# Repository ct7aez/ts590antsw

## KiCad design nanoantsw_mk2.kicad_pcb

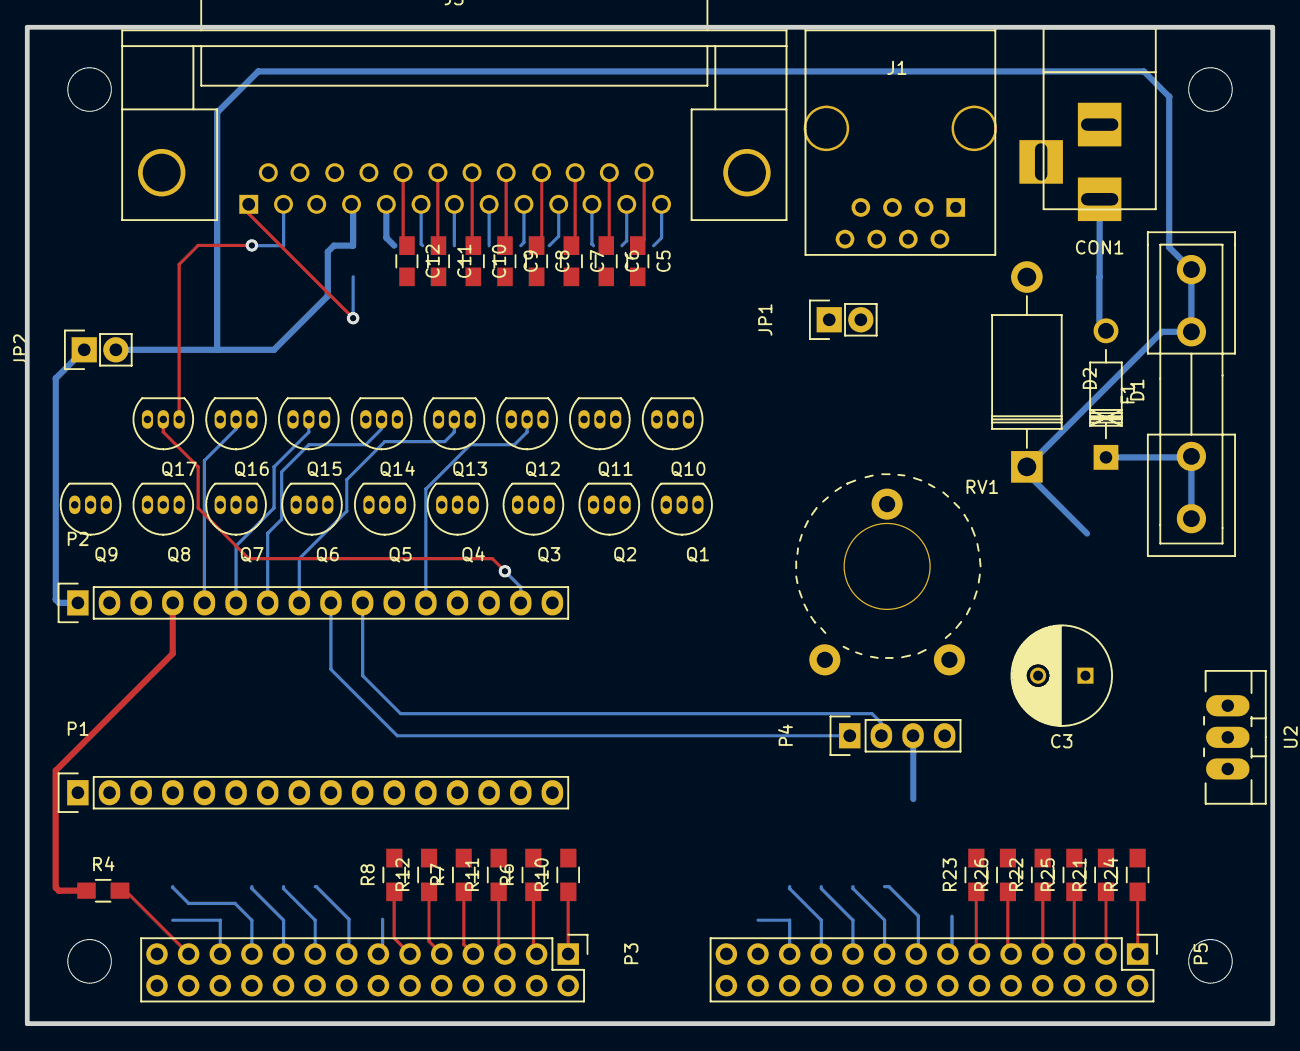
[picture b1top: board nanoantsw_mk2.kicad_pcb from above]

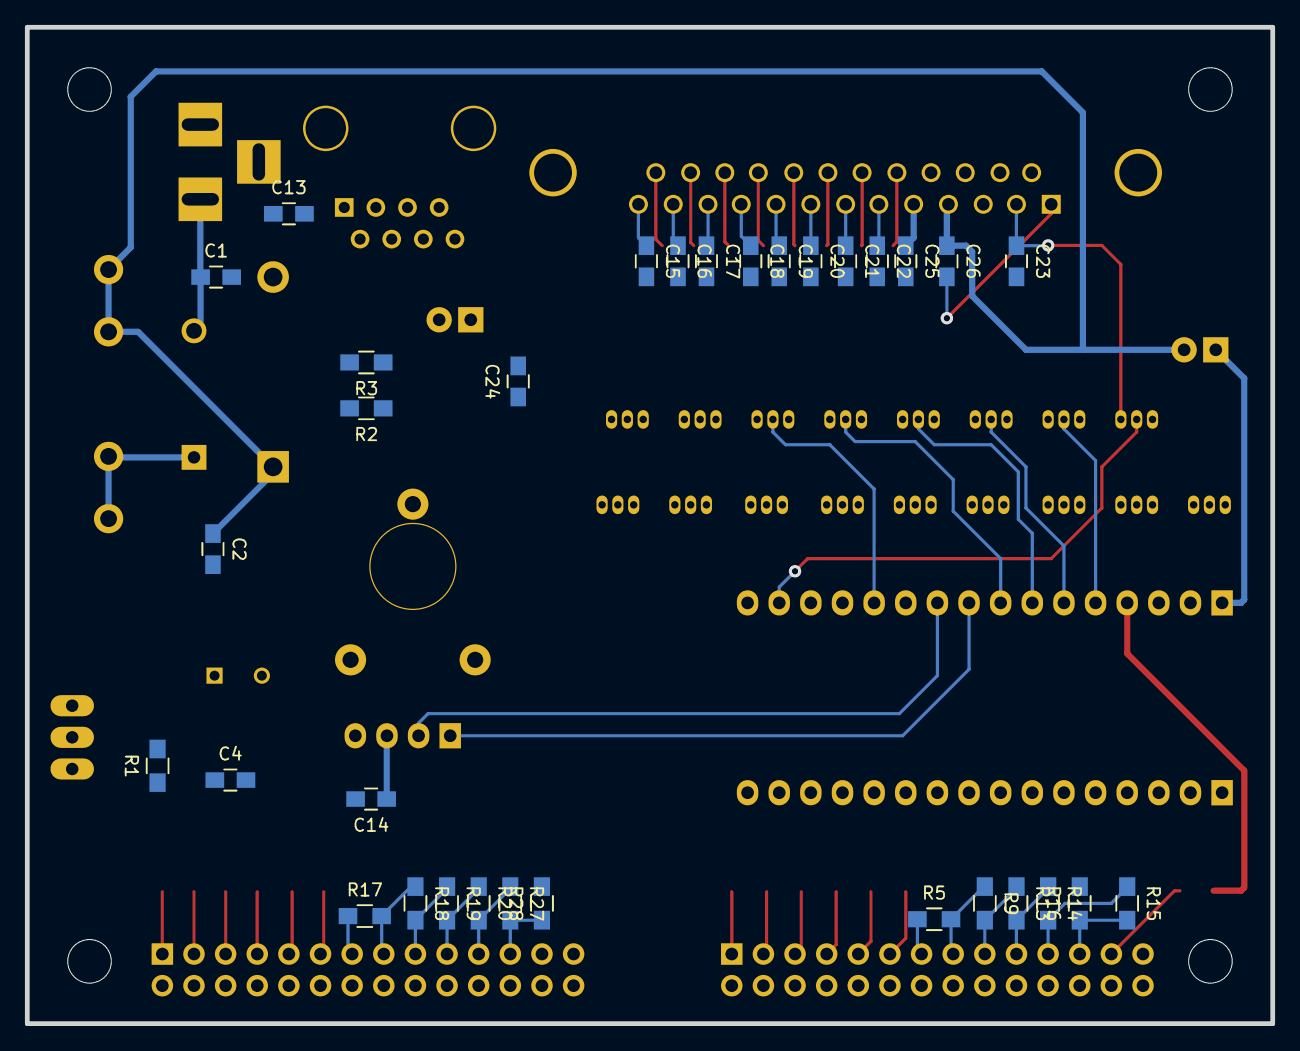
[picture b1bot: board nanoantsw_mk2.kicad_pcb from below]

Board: 2 copper layers, 100.0 x 80.0 mm, 86 parts (32 on the bottom side), 71 nets.

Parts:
C1: 4n7; C_0805_HandSoldering
C2: 330n; C_0805_HandSoldering
C3: 220u; C_Radial_D8_L21_P3.8
C4, C25, C26: 100n; C_0805_HandSoldering
C5, C6, C7, C8, C9, C10, C11, C12, C13, C14, C15, C16, C17, C18, C19, C20, C21, C22, C23, C24: 10n; C_0805_HandSoldering
CON1: 5,5/2,1mm; BARREL_JACK
D1: 1N5817; Diode_DO-41_SOD81_Horizontal_RM10
D2: 1.5KE20A; Diode_DO-201AD_Horizontal_RM15
F1: 500mAT; Fuseholder5x20_horiz_open_inline_Type-I
J1: RJ45; RJ45_8
J3: DB25; DB25FC
JP1, JP2: Jumper_NO_Small; Pin_Header_Straight_1x02
P1, P2: CONN_01X16; Socket_Strip_Straight_1x16
P3, P5: CONN_02X14; Pin_Header_Straight_2x14
P4: CONN_01X04; Pin_Header_Straight_1x04
Q1, Q2, Q3, Q4, Q5, Q6, Q7, Q8, Q9, Q10, Q11, Q12, Q13, Q14, Q15, Q16, Q17: BS170; TO-92_Inline_Narrow_Oval
R1: 240R; R_0805_HandSoldering
R2, R3: 2K; R_0805_HandSoldering
R4, R16: 3K3; R_0805_HandSoldering
R5: 100R; R_0805_HandSoldering
R6, R7, R8, R10, R11, R12, R21, R22, R23, R24, R25, R26: 330R; R_0805_HandSoldering
R9: 200R; R_0805_HandSoldering
R13: 390R; R_0805_HandSoldering
R14: 820R; R_0805_HandSoldering
R15: 1K6; R_0805_HandSoldering
R17: 6K8; R_0805_HandSoldering
R18: 13K; R_0805_HandSoldering
R19: 27K; R_0805_HandSoldering
R20: 62K; R_0805_HandSoldering
R27: 120K; R_0805_HandSoldering
R28: 240K; R_0805_HandSoldering
RV1: 5K; Potentiometer_Trimmer-Piher_PT15-V12-5_horizontal_revers
U2: LM317AT; TO-220_Neutral123_Vertical_LargePads

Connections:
+5V: C14.1, J1.2, JP1.1, P2.4, P4.3, R4.1
/2M: C22.1, J3.6, Q15.1
/4M: C11.1, J3.19, Q14.1
/6M: C21.1, J3.7, Q13.1
/10M: C10.1, J3.20, Q12.1
/12M: C20.1, J3.8, Q11.1
/15M: C9.1, J3.21, Q10.1
/17M: C19.1, J3.9, Q9.1
/20M: C8.1, J3.22, Q8.1
/30M: C18.1, J3.10, Q7.1
/40M: C7.1, J3.23, Q6.1
/60M: C17.1, J3.11, Q5.1
/80M: C6.1, J3.24, Q4.1
/137KHz: C15.1, J3.13, Q1.1
/160M: C16.1, J3.12, Q3.1
/472KHz: C5.1, J3.25, Q2.1
/A0: P2.5, Q16.2
/A1: P2.6, Q15.2
/A2: P2.7, Q14.2
/A3: P2.8, Q13.2
/A7: P2.12, Q12.2, R8.2
/AUX: C12.1, J3.18, Q16.1
/BNDSW: P2.11, P3.13, P3.25, R4.2, R5.1
/D2: P1.5, Q1.2, R24.2
/D3: P1.6, Q2.2, R21.2
/D4: P1.7, Q3.2, R10.2
/D5: P1.8, Q4.2, R6.2
/D6: P1.9, Q5.2, R25.2
/D7: P1.10, Q6.2, R11.2
/D8: P1.11, Q7.2, R22.2
/D9: P1.12, Q8.2, R7.2
/D10: P1.13, Q9.2, R26.2
/D11: P1.14, Q10.2, R12.2
/D12: P1.15, Q11.2, R23.2
/D13: P2.15, Q17.2
/ENBL: C23.1, J3.2, Q17.1
/EXT_SCL: C24.1, J1.5, P2.10, P4.2, R3.2
/EXT_SDA: C13.1, J1.4, P2.9, P4.1, R2.2
/SW1a: P5.13, R16.2, R17.1
/SW2: P3.15, R5.2, R9.1
/SW2b: P5.15, R17.2, R18.1
/SW3: P3.17, R9.2, R13.1
/SW3c: P5.17, R18.2, R19.1
/SW4: P3.19, R13.2, R14.1
/SW4d: P5.19, R19.2, R20.1
/SW5: P3.21, R14.2, R15.1
/SW5e: P5.21, R20.2, R27.1
/SW6: P3.23, R15.2, R16.1
/SW6f: P5.23, R27.2, R28.1
GND: C13.2, C14.2, C24.2, J1.7, P1.4, P2.2, P3.2, P3.4, P3.6, P3.8, P3.10, P3.12, P3.14, P3.16, P3.18, P3.20, P3.22, P3.24, P3.26, P4.4, P5.2, P5.4, P5.6, P5.8, P5.10, P5.12, P5.14, P5.16, P5.18, P5.20, P5.22, P5.24, R28.2
GNDA: C1.2, C2.2, C3.2, C4.2, C5.2, C6.2, C7.2, C8.2, C9.2, C10.2, C11.2, C12.2, C15.2, C16.2, C17.2, C18.2, C19.2, C20.2, C21.2, C22.2, C23.2, CON1.2, D2.2, Q1.3, Q2.3, Q3.3, Q4.3, Q5.3, Q6.3, Q7.3, Q8.3, Q9.3, Q10.3, Q11.3, Q12.3, Q13.3, Q14.3, Q15.3, Q16.3, Q17.3, RV1.1, RV1.2
unnamed: C1.1, CON1.1, D1.2
unnamed: C25.2, C26.2, J3.1
unnamed: D1.1, F1.1
unnamed: JP1.2, R2.1, R3.1
unnamed: JP2.1, P2.1
unnamed: P3.1, R10.1
unnamed: P3.3, R6.1
unnamed: P3.5, R11.1
unnamed: P3.7, R7.1
unnamed: P3.9, R12.1
unnamed: P3.11, R8.1
unnamed: P5.1, R24.1
unnamed: P5.3, R21.1
unnamed: P5.5, R25.1
unnamed: P5.7, R22.1
unnamed: P5.9, R26.1
unnamed: P5.11, R23.1
unnamed: R1.2, RV1.3, U2.1
VCC: C2.1, C26.1, D2.1, F1.2, J3.4, JP2.2, U2.3
VEE: C3.1, C4.1, C25.1, J3.5, R1.1, U2.2

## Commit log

2015-07-21 kick off
